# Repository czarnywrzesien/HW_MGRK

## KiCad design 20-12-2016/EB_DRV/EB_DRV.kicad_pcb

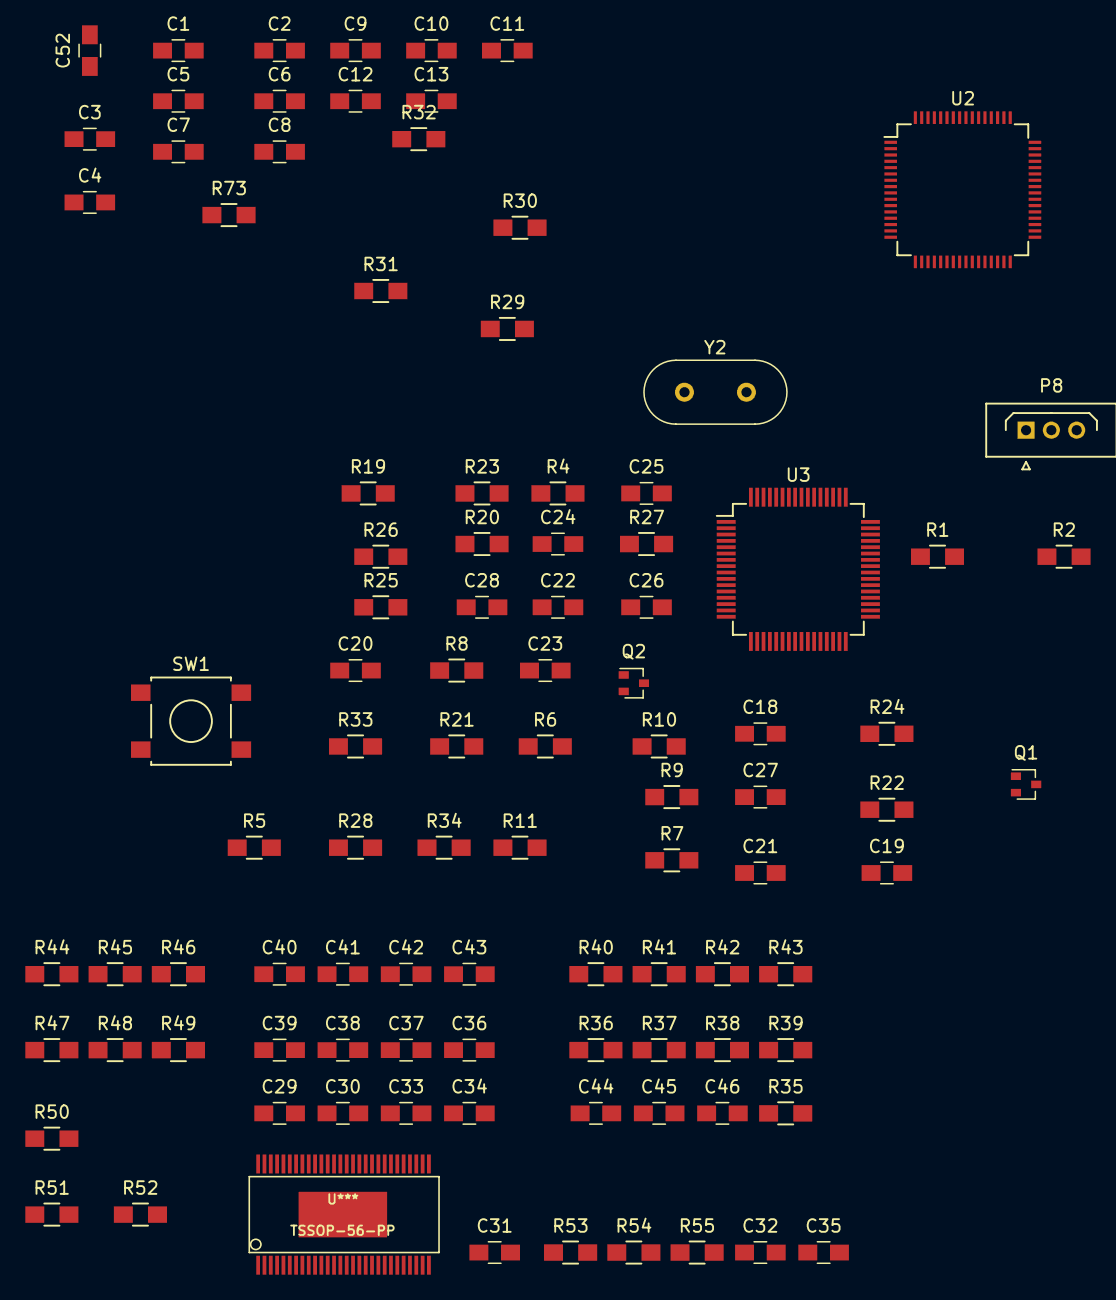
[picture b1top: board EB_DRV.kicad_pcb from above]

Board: 2 copper layers, 99 parts (0 on the bottom side), 55 nets, no tracks yet.

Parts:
C1, C2, C3, C4, C5, C6, C7, C8, C9, C13, C18, C21, C22, C25, C26, C27, C52: 100n; C_0805_HandSoldering
C10: 1u; C_0805_HandSoldering
C11, C12: 20p; C_0805_HandSoldering
C19, C20, C23, C24, C44, C45: C; C_0805_HandSoldering
C28: 4,7u; C_0805_HandSoldering
C29, C34: 1uF; C_0805_HandSoldering
C30: 2,2uF; C_0805_HandSoldering
C31: 6800pF; C_0805_HandSoldering
C32: 0.022uF; C_0805_HandSoldering
C33: 120pF; C_0805_HandSoldering
C35: 0,015uF; C_0805_HandSoldering
C36, C42: 0,1uF; C_0805_HandSoldering
C37, C38, C39, C40: 0,1u; C_0805_HandSoldering
C41, C43: 4,7uF; C_0805_HandSoldering
C46: 47uF; C_0805_HandSoldering
P8: CONN_01X03; Harwin_LTek-Male_03x2.00mm_Straight
Q1, Q2: Q_NPN_BCE; SOT-323
R1, R2: 1,5k; R_0805_HandSoldering
R4, R19, R20, R21, R22, R23, R24, R25, R26, R27, R28, R29, R30, R31, R32, R39, R40, R50, R51, R52, R53, R54, R55, R73: R; R_0805_HandSoldering
R5, R6: 22R; R_0805_HandSoldering
R7, R8, R9: 100R; R_0805_HandSoldering
R10, R11: SHUNT; R_0805_HandSoldering
R33: 220; R_0805_HandSoldering
R34: 2k; R_0805_HandSoldering
R35, R37: 10k; R_0805_HandSoldering
R36: 31,6k; R_0805_HandSoldering
R38: 16,2k; R_0805_HandSoldering
R41: 1; R_0805_HandSoldering
R42: 205k; R_0805_HandSoldering
R43: 1M; R_0805_HandSoldering
R44, R46, R48: 39k; R_0805_HandSoldering
R45, R47, R49: 2k2; R_0805_HandSoldering
SW1: SW_PUSH; SW_SPST_B3S-1000
TSSOP-56-PP: U***; TSSOP-56-PP
U2: STM32F401RBT6; LQFP-64_10x10mm_Pitch0.5mm
U3: STM32F100RBT6; TQFP-64_10x10mm_Pitch0.5mm
Y2: Crystal_Small; Crystal_HC18-U_Vertical

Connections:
+3V3: C1.1, C2.1, C3.1, C4.1, C5.1, C6.1, C7.1, C8.1, C10.1, C24.1, C52.1, P8.1, R1.1, R2.1, R9.1, R19.2, R22.1, R26.1, R27.1, R35.1, R36.1, U2.1, U2.13, U2.19, U2.32, U2.48, U2.64, U3.1, U3.13, U3.19, U3.32, U3.48, U3.64
+5V: R29.1, R30.1, R31.1, R32.1, R73.1
+36V: C36.1, C41.1, C42.1, C43.1
/Bike_sensors/FRONT_BREAK: R31.2, U2.61
/Bike_sensors/REAR_BREAK: R32.2, U2.62
/Bike_sensors/SPEED: R73.2, U2.8
/Light_sensor/L_SIGNAL: R33.2, U3.8
/Lights_driver/ST_3V2: C21.1, C22.1, C25.1, C26.1, C27.1, C28.1
/Lights_driver/ST_RESET2: C18.1, R19.1, SW1.1, U3.7
/MCU/BR_S01: R39.2, U2.23
/MCU/BR_S02: R40.2, U2.24
/MCU/FAULT: R35.2, U2.29
/MCU/I2C_DATA: R2.2, U2.59, U3.30
/MCU/I2C_SCK: R1.2, U2.58, U3.29
/MCU/LED_GREEN: R8.1, U2.56
/MCU/LED_RED: R7.1, U2.57
/MCU/SENS1: R44.1, R45.1, U2.20
/MCU/SENS2: R46.1, R47.1, U2.21
/MCU/SENS3: R48.1, R49.1, U2.22
/MCU/ST_RESET1: C9.2, U2.7
/MCU/USB_DM: R5.1, U2.44
/MCU/USB_DP: R6.1, U2.45
/MOSFET_PWR/H1_LOW: R10.1, R52.1
/MOSFET_PWR/H1_VS: C37.1, R44.2
/MOSFET_PWR/H2_VS: C38.1, R46.2
/MOSFET_PWR/H3_LOW: R11.1, R50.1
/MOSFET_PWR/H3_VS: C39.1, R48.2
/T1: R25.2, U3.51
/T2: R28.1, U3.52
GND: C1.2, C2.2, C3.2, C4.2, C5.2, C6.2, C7.2, C8.2, C9.1, C10.2, C11.1, C12.1, C13.2, C18.2, C19.1, C20.1, C21.2, C22.2, C25.2, C26.2, C27.2, C28.2, C29.2, C30.2, C31.2, C33.2, C34.2, C35.1, C36.2, C41.2, C42.2, C43.2, C46.2, C52.2, Q1.3, Q2.3, R4.1, R23.2, R24.2, R34.2, R37.2, R41.2, R42.2, R43.1, R55.2, SW1.2, U2.12, U2.18, U2.31, U2.47, U2.60, U2.63, U3.12, U3.18, U3.31, U3.63
GNDA: R10.2, R11.2, R45.2, R47.2, R49.2, R51.1, R53.1
unnamed: C11.2, U2.6
unnamed: C12.2, U2.5
unnamed: C13.1, U2.30
unnamed: C19.2, U3.6, Y2.1
unnamed: C20.2, U3.5, Y2.2
unnamed: C23.1, R22.2
unnamed: C23.2, P8.2, R21.1, R23.1
unnamed: C24.2, P8.3, R20.1, R24.1
unnamed: C31.1, R38.2
unnamed: C33.1, R38.1
unnamed: C44.1, R52.2
unnamed: C44.2, R53.2
unnamed: C45.1, R50.2
unnamed: C45.2, R51.2
unnamed: C46.1, R54.1
unnamed: Q1.2, R26.2
unnamed: Q2.2, R27.2
unnamed: R33.1, R34.1
unnamed: Q1.1, R25.1
unnamed: Q2.1, R28.2
unnamed: R20.2, U3.33
unnamed: R21.2, U3.34
unnamed: R36.2, R37.1
unnamed: R54.2, R55.1

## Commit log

2017-01-23 Initial creation
2017-01-23 Added_footprints(not all)
